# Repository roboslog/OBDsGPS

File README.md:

# OBDsGPS

OBD ii GPS tracker is the most convenient vehicle GPS tracking device. This tracker plugs into a vehicle’s OBD II port for easy installation. The OBD ii tracker installs within seconds and runs itself. OBD tracker can be used in any car or van manufactured after 2000.

Why we need OBD?

SPEED ALERT BETA
 “The device can be set to alert you when the vehicle exceeds the posted speed limit of whatever road it is currently travelling on.

SPEED THRESHOLD
 The device can be set to alert you whenever the vehicle exceeds a certain speed.

HARSH BRAKING
 The device tracks the rate of deceleration of the vehicle, a major indicator of aggressive driving, and alerts you when the vehicle exceeds a safe threshold.

RAPID ACCELERATION
Another major indicator of aggressive driving, the device also tracks the rate of acceleration of the vehicle and alerts you when the vehicle exceeds a safe threshold.”

OBD-II Background
The OBD-II specification is controlled by the Society of Automobile Engineers and defines the method for requesting diagnostic data and provides a list of standard parameters from the engine control unit. The specification was first released in 1979. Today, depending upon the vehicle, the tracker can retrieve values that include: throttle, engine RPM, fuel available. In some vehicles, the device can even retrieve engine diagnostic codes.

Where is my OBD-II Port?
The OBD-II diagnostic port, also known as a Data Link Connector (DLC), is generally located on the driver’s side of the car or truck under the dash. The location will vary between different manufacturers, models, and production years of a car or truck model. 

Testing Tracking Device Installation
With the creation of your account, a username and password were sent to you for our tracking website. Logon to the system and go to the reports section. Run the unit list view report. Check to be sure the tracking device is reporting ignition on/off events.

What else OBD can do ?
1.Read error diagnostic code

2.Clear the fault code (clear the error code and turn off MIL)

3.Engine revolutions per minute (RPM)

4.Calculated load value

5.Coolant temperature

6.Fuel system status

7.Speed

8.Short-term fuel situation

9.Long-term fuel situation

10.Intake manifold pressure

11.Fuel injection advance time

12.Intake air temperature

& Many more….

Our all files & Code here are For Non-Commercial (Educational) use Only, For Commercial Use: Give Credit to ROBOSLOG
Thanks
More updates coming soon..

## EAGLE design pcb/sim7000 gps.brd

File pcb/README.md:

Features:
1.Firmware Version V1.5 (Supports more protocols SAE J1850 than V2.1).
2.With chip:PIC18F25K80  ,supports all ELM327 fucntions,in program ELM327 identifier,it shows full functions.
It understand commands such as  ATPPS and other. 
The frequency of the crystal oscillator is 4mHz.

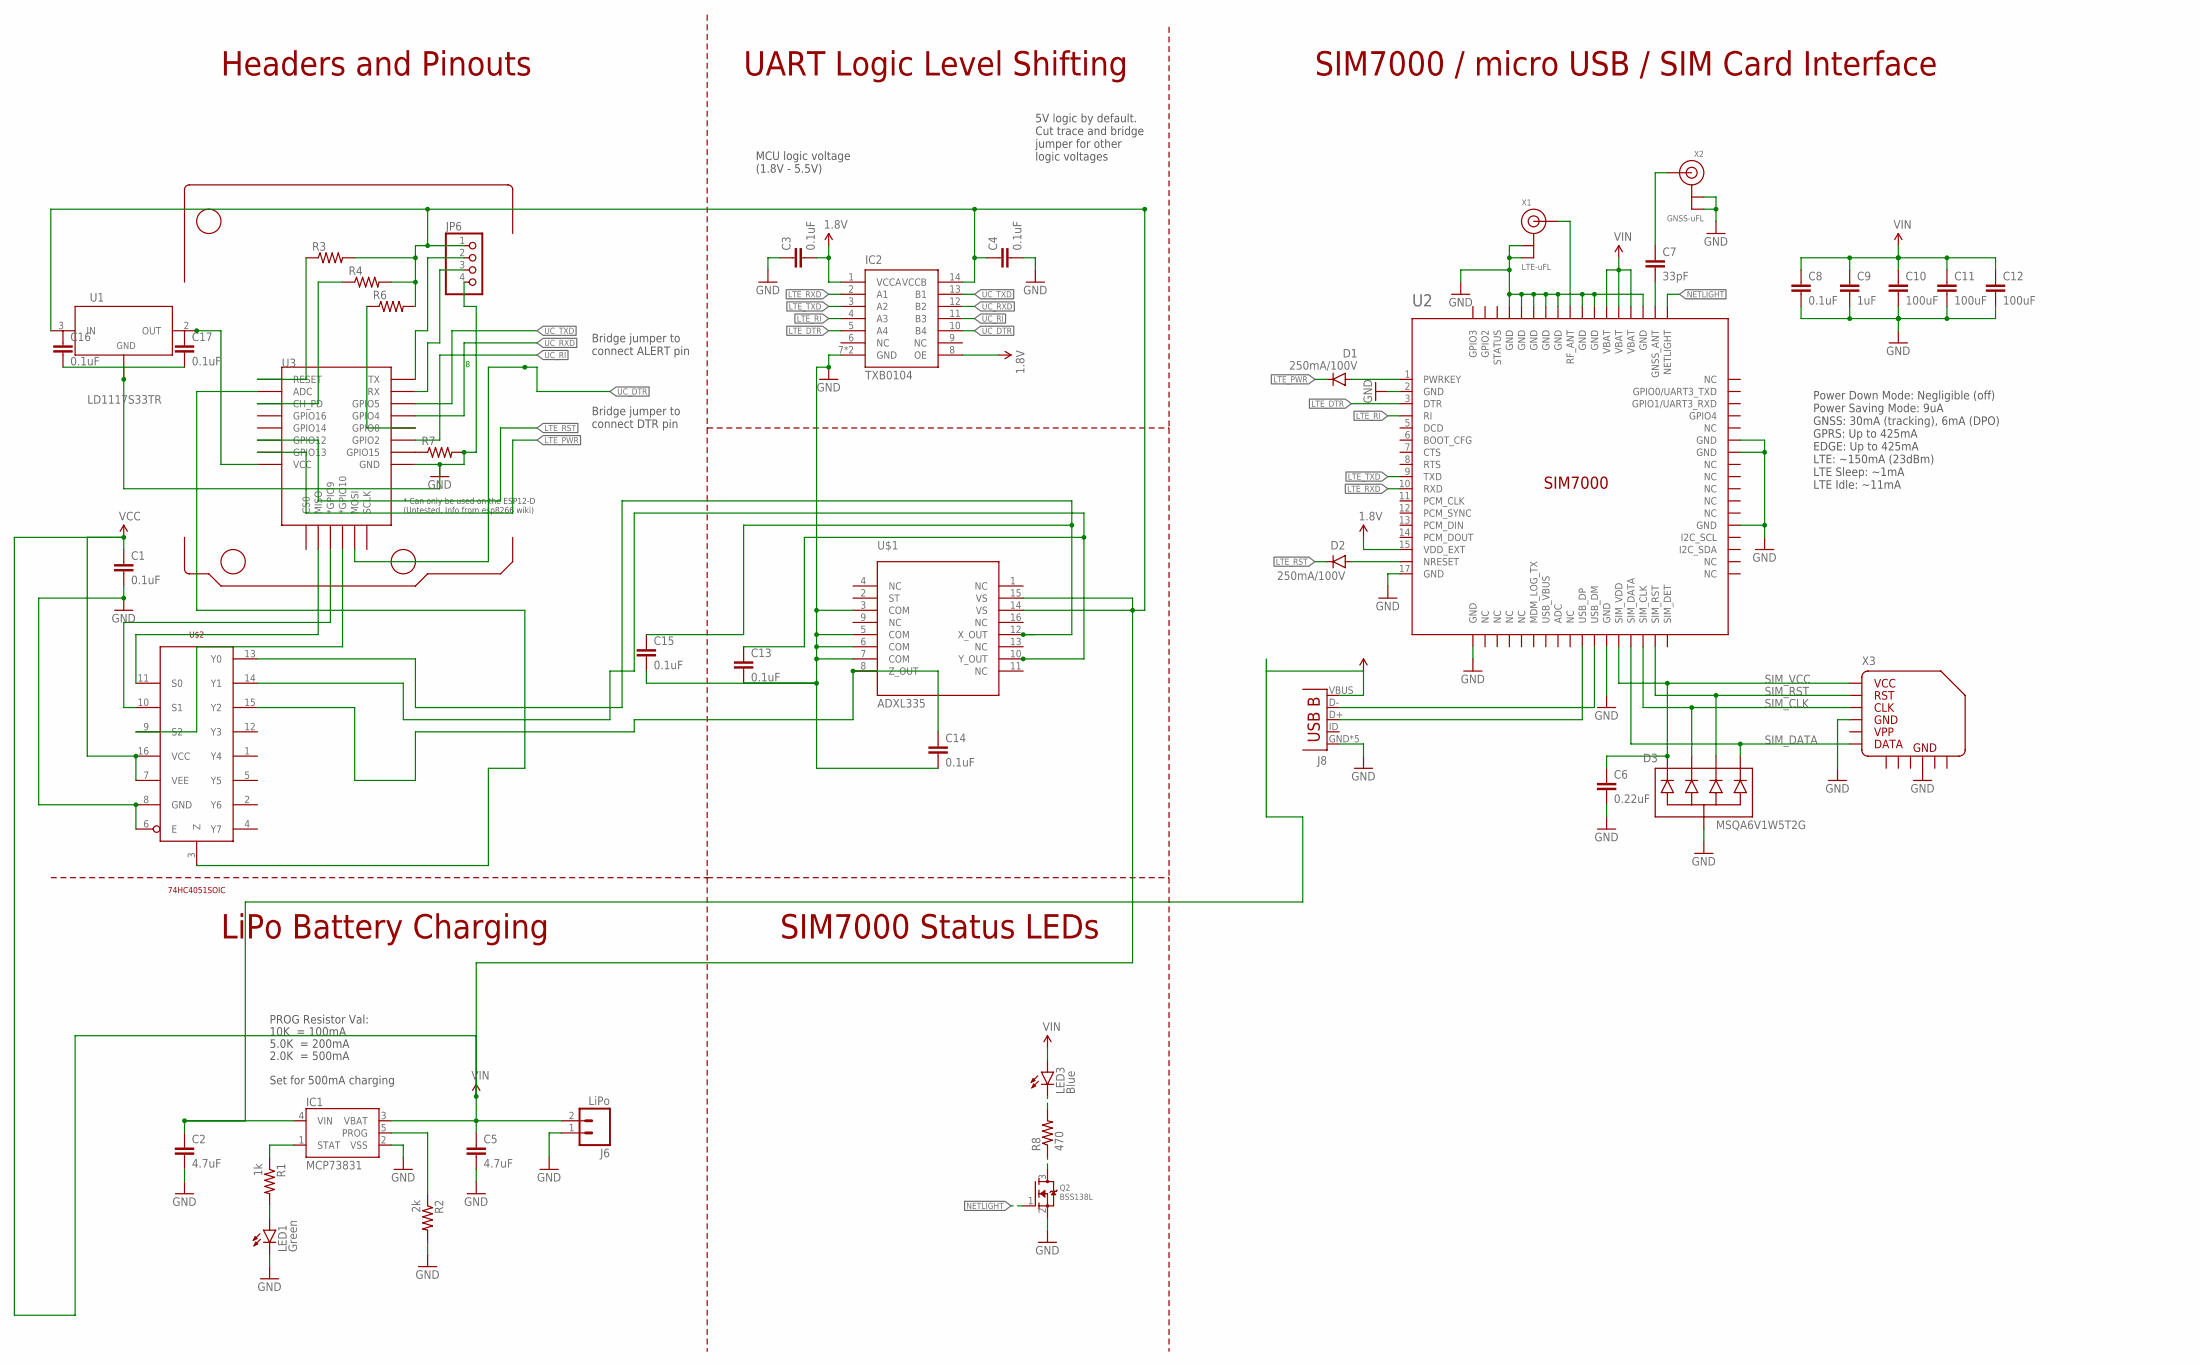
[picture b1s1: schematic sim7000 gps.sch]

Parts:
C1, C16, C17: 0.1uF; 0603
C2, C5: 4.7uF; 0603-CAP-MARKED
C3, C4, C8, C13, C14, C15: 0.1uF; 0603-CAP-MARKED
C6: 0.22uF; 0603-CAP-MARKED
C7: 33pF; 0603-CAP-MARKED
C9: 1uF; 0603-CAP-MARKED
C10, C11, C12: 100uF; 1210
D1, D2: 250mA/100V; SOD-323
D3: MSQA6V1W5T2G; SOT-353
IC1: MCP73831; SOT23-5
IC2: TXB0104; VQFN-14
J6: LiPo; JST-2-SMD
J8: microUSB; USB-B-MICRO-SMD
JP6: PINHD-1X4; 1X04
LED1: Green; LED-0603-MARKED
LED3: Blue; LED-0603-MARKED
Q2: BSS138L; SOT23-3
R1: 1k; 0603-RES-MARKED
R2: 2k; 0603-RES-MARKED
R3, R4, R6, R7: R-US_R0603; R0603
R8: 470; 0603-RES-MARKED
U1: LD1117S33TR; SOT-223
U2: SIM7000
U3: ESP12ESMD; ESP12E-SMD
U$1: ADXL335; LFCSP16
U$2: 74HC4051SOIC; SOIC-16_3.9MM
X1: LTE-uFL; U.FL
X2: GNSS-uFL; U.FL
X3: MICROSIM_SOCKET_PUSH-PULL

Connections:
1.8V: C3.2, IC2.1 (VCCA), IC2.8 (OE), U2.15 (VDD_EXT)
GND: C1.2, C2.2, C3.1, C4.2, C5.2, C6.2, C8.2, C9.2, C10.2, C11.2, C12.2, C13.2, C14.2, C15.2, C16.2, C17.2, D3.2 (COM), IC1.2 (VSS), IC2.7 (GND), IC2.PAD (GND), J6.1 (2), J8.GND, J8.SHIELD1 (GND), J8.SHIELD2 (GND), J8.SHIELD3 (GND), J8.SHIELD4 (GND), JP6.4, LED1.C, Q2.2 (S), R2.2, R7.2, U1.1 (ADJ/GND), U2.2 (GND), U2.17 (GND), U2.18 (GND), U2.29 (GND), U2.39 (GND), U2.45 (GND), U2.46 (GND), U2.54 (GND), U2.58 (GND), U2.59 (GND), U2.61 (GND), U2.62 (GND), U2.63 (GND), U2.64 (GND), U2.65 (GND), U3.GND, U$1.3 (COM), U$1.5 (COM), U$1.6 (COM), U$1.7 (COM), U$2.6 (E), U$2.8 (GND), X1.1 (GND), X1.2 (GND), X2.1 (GND), X2.2 (GND), X3.C5, X3.GND@1 (GND), X3.GND@2 (GND), X3.GND@3 (GND), X3.GND@4 (GND), X3.GND@5 (GND), X3.GND@6 (GND)
LTE_DTR: IC2.5 (A4), U2.3 (DTR)
LTE_PWR: D1.C, U3.GPIO13
LTE_RI: IC2.4 (A3), U2.4 (RI)
LTE_RST: D2.C, U3.GPIO12
LTE_RXD: IC2.2 (A1), U2.10 (RXD)
LTE_TXD: IC2.3 (A2), U2.9 (TXD)
unnamed: C7.2, U2.53 (GNSS_ANT)
unnamed: D1.A, U2.1 (PWRKEY)
unnamed: C7.1, X2.3 (SIGNAL)
unnamed: U3.MISO, U$2.11 (S0)
unnamed: U3.GPIO9 (*GPIO9), U$2.10 (S1)
unnamed: R7.1, U3.GPIO15
unnamed: J8.D-, U2.28 (USB_DM)
unnamed: J8.D+, U2.27 (USB_DP)
unnamed: Q2.3 (D), R8.1
unnamed: LED3.C, R8.2
unnamed: U3.GPIO10 (*GPIO10), U$2.9 (S2)
unnamed: R3.1, U3.RESET
unnamed: LED1.A, R1.2
unnamed: R4.1, U3.CH_PD
unnamed: C14.1, U$1.8 (Z_OUT), U$2.15 (Y2)
unnamed: U1.2 (OUT), U1.4, U3.VCC
unnamed: R6.1, U3.GPIO0
unnamed: C13.1, U$1.10 (Y_OUT), U$2.14 (Y1)
unnamed: C15.1, U$1.12 (X_OUT), U$2.13 (Y0)
unnamed: JP6.2, U3.TXD0 (TX)
unnamed: JP6.3, U3.RXD0 (RX)
unnamed: U3.ADC, U$2.3 (Z)
NETLIGHT: Q2.1 (G), U2.52 (NETLIGHT)
NRESET: D2.A, U2.16 (NRESET)
PROG: IC1.5 (PROG), R2.1
RF_ANT: U2.60 (RF_ANT), X1.3 (SIGNAL)
SIM_CLK: D3.3 (2), U2.32 (SIM_CLK), X3.C3
SIM_DATA: D3.5 (4), U2.31 (SIM_DATA), X3.C7
SIM_RST: D3.4 (3), U2.33 (SIM_RST), X3.C2
SIM_VCC: C6.1, D3.1, U2.30 (SIM_VDD), X3.C1
STAT: IC1.1 (STAT), R1.1
UC_DTR: IC2.10 (B4), U3.MOSI
UC_RI: IC2.11 (B3), U3.GPIO2
UC_RXD: IC2.12 (B2), U3.GPIO4
UC_TXD: IC2.13 (B1), U3.GPIO5
VIN: C1.1, C4.1, C5.1, C8.1, C9.1, C10.1, C11.1, C12.1, IC1.3 (VBAT), IC2.14 (VCCB), J6.2 (1), JP6.1, LED3.A, R3.2, R4.2, R6.2, U1.3 (IN), U2.55 (VBAT), U2.56 (VBAT), U2.57 (VBAT), U$1.14 (VS), U$1.15 (VS), U$2.7 (VEE), U$2.16 (VCC)
V_USB: C2.1, IC1.4 (VIN), J8.VBUS

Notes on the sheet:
SIM7000 / micro USB / SIM Card Interface
Headers and Pinouts
LiPo Battery Charging
UART Logic Level Shifting
SIM7000 Status LEDs
Power Down Mode: Negligible (off) Power Saving Mode: 9uA GNSS: 30mA (tracking), 6mA (DPO) GPRS: Up to 425mA EDGE: Up to 425mA LTE: ~150mA (23dBm) LTE Sleep: ~1mA LTE Idle: ~11mA
Bridge jumper to connect DTR pin
Bridge jumper to connect ALERT pin
MCU logic voltage (1.8V - 5.5V)
5V logic by default. Cut trace and bridge jumper for other logic voltages
Set for 500mA charging
10K = 100mA
5.0K = 200mA
2.0K = 500mA
PROG Resistor Val:

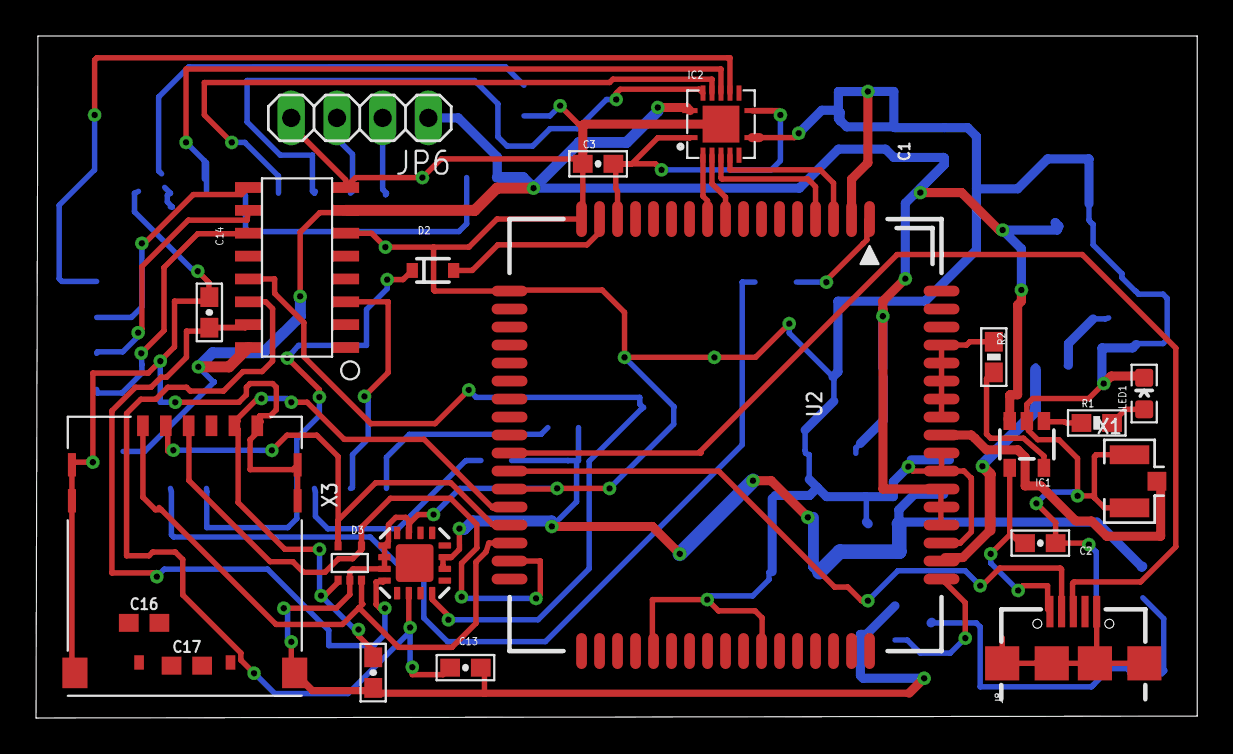
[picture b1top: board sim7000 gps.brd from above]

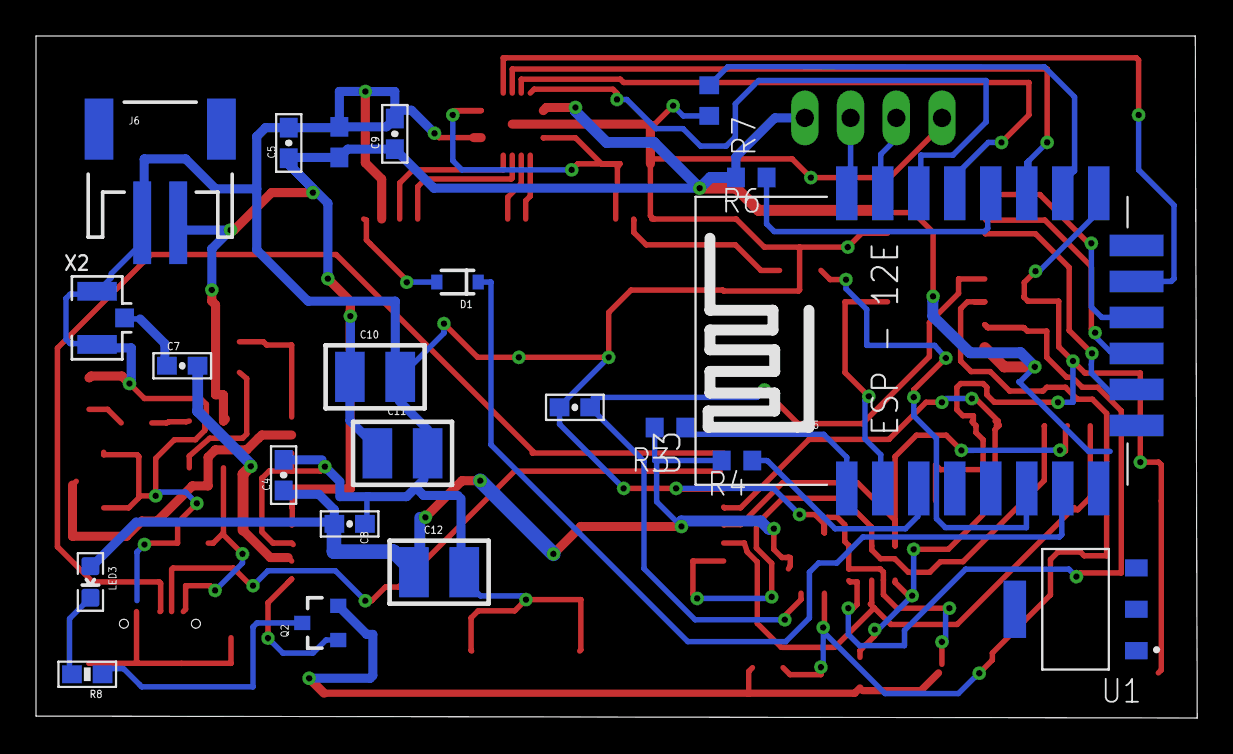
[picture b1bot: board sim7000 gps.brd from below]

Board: 2 copper layers, 64.5 x 37.9 mm, 43 parts (22 on the bottom side), 45 nets.

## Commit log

2020-05-05 OBD Main file For sending OBD data to Server
    OBD ii GPS tracker is the most convenient vehicle GPS tracking device. This tracker plugs into a vehicle’s OBD II port for easy installation. The OBD ii tracker installs within seconds and runs itsel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
2020-05-14 Update README.md
    Non-commercial

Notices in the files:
parts and their libraries:
SparkFun-Capacitors: Licensing: Creative Commons ShareAlike 4.0 International - https://creativecommons.org/licenses/by-sa/4.0
